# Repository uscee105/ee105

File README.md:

---
layout: home
title: USC EE 105
nav_exclude: true
permalink: /:path/
seo:
  type: Course
  name: EE 105
---

# Course website for USC EE 105

This introductory course offers a broad overview of electronic systems, integrating both hardware and software perspectives. Students will explore the fundamental building blocks of electronics, including basic circuits and key components such as resistors, capacitors, inductors, diodes, transistors, optoelectronic devices, and sensors. A central feature of the course is the hands-on design, construction, and testing of an optical biosensor that synthesizes concepts learned throughout the semester. Students will also be introduced to foundational topics in signals and systems, as well as neural networks, culminating in the implementation of a simple image classification system using embedded machine learning. Another major focus is on communication systems, particularly free-space optical communication, where students will build and experiment with paired light emitters and detectors. Hands-on learning is supported by a custom demonstration board, which includes modules for circuits, devices, system integration, and AI/ML-based image processing. In summary, this course provides an engaging introduction to electrical engineering, emphasizing experiential learning through the development of intelligent hardware and software systems.

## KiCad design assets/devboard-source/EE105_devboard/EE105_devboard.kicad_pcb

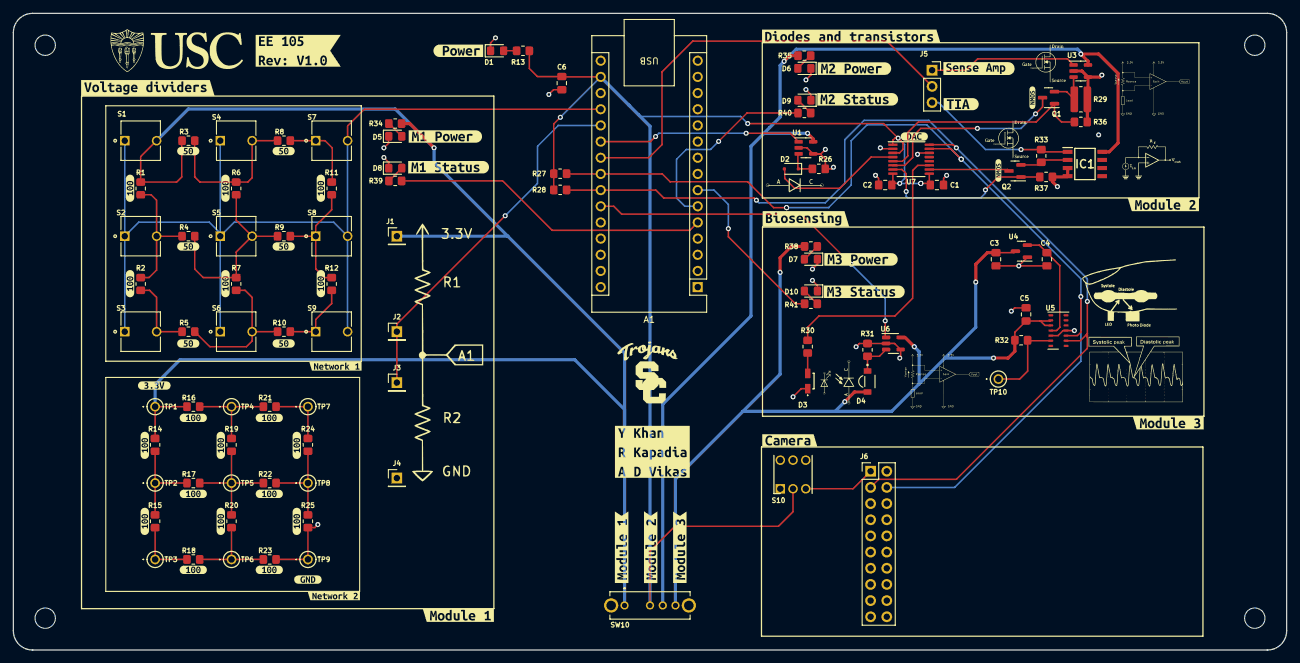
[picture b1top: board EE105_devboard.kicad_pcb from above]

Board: 2 copper layers, 200.0 x 100.0 mm, 150 parts (0 on the bottom side), 52 nets.

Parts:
A1: Arduino_Nano_Every; Arduino_Nano
C1, C5: 0.1uF; C_0805_2012Metric_Pad1.18x1.45mm_HandSolder
C2: 100nF; C_0805_2012Metric_Pad1.18x1.45mm_HandSolder
C3, C4, C6: 1uF; C_0805_2012Metric_Pad1.18x1.45mm_HandSolder
D1: PWR; LED_0805_2012Metric_Pad1.15x1.40mm_HandSolder
D2: D; D_SOD-323F
D3: PD_LED; CSL0416WBCW1
D4: VEMD2023SLX01; XDCR_VEMD2023SLX01
D5: m1_pwr; LED_0805_2012Metric_Pad1.15x1.40mm_HandSolder
D6: m2_pwr; LED_0805_2012Metric_Pad1.15x1.40mm_HandSolder
D7: m3_pwr; LED_0805_2012Metric_Pad1.15x1.40mm_HandSolder
D8: m1_status; LED_0805_2012Metric_Pad1.15x1.40mm_HandSolder
D9: m2_status; LED_0805_2012Metric_Pad1.15x1.40mm_HandSolder
D10: m3_status; LED_0805_2012Metric_Pad1.15x1.40mm_HandSolder
H1, H2, H3, H4: MountingHole; MountingHole_3.2mm_M3
IC1: TLV9102IDR; SOIC127P600X175-8N
J1, J2, J3, J4: Conn_01x01_Pin; PinHeader_1x01_P2.54mm_Vertical
J5: tia vs senseamp; PinSocket_1x03_P2.54mm_Vertical
J6: camera_connector; PinHeader_2x10_P2.54mm_Vertical
Q1, Q2: DMN3404L; SOT-23
R1, R2, R6, R7, R11, R12, R14, R15, R16, R17, R18, R19, R20, R21, R22, R23, R24, R25: 100; R_0805_2012Metric_Pad1.20x1.40mm_HandSolder
R3, R4, R5, R8, R9, R10: 50; R_0805_2012Metric_Pad1.20x1.40mm_HandSolder
R13, R30, R31, R34, R35, R36, R37, R38, R39, R40, R41: 1k; R_0805_2012Metric_Pad1.20x1.40mm_HandSolder
R26: 0.2; R_0805_2012Metric_Pad1.20x1.40mm_HandSolder
R27, R28: 4.7k; R_0805_2012Metric_Pad1.20x1.40mm_HandSolder
R29: 0.04; R_0815_2038Metric_Pad1.20x4.05mm_HandSolder
R32: 10k; R_0805_2012Metric_Pad1.20x1.40mm_HandSolder
R33: 1; R_0805_2012Metric_Pad1.20x1.40mm_HandSolder
S1, S2, S3, S4, S5, S6, S7, S8, S9: 4-1437565-0; SW_4-1437565-0
S10: MHPS2266; DIPS450W80P200L600H1050Q6N
SW10: pwr_select; OS103011MA7QP1
TP1, TP2, TP3, TP4, TP5, TP6, TP7, TP8, TP9, TP10: 5115
U1, U3, U6: INA180A1; SOT-23-5
U4: MCP1703T-1802E/CB; SOT-23
U5: MAX30102; Maxim_OLGA-14_3.3x5.6mm_P0.8mm
U7: AD5593R; TSSOP-16_4.4x5mm_P0.65mm
kibuzzard-666A1C01: G***; kibuzzard-666A1C01
kibuzzard-666A1C15: G***; kibuzzard-666A1C15
kibuzzard-666A1C72: G***; kibuzzard-666A1C72
kibuzzard-666A1D09: G***; kibuzzard-666A1D09
kibuzzard-666A1E2E: G***; kibuzzard-666A1E2E
kibuzzard-666A1E14: G***; kibuzzard-666A1E14
kibuzzard-666A1E29: G***; kibuzzard-666A1E29
kibuzzard-666A13FA: G***; kibuzzard-666A13FA
kibuzzard-666A15EB: G***; kibuzzard-666A15EB
kibuzzard-666A140F: G***; kibuzzard-666A140F
kibuzzard-666A176F: G***; kibuzzard-666A176F
kibuzzard-666A1613: G***; kibuzzard-666A1613
kibuzzard-666A1764: G***; kibuzzard-666A1764
kibuzzard-666B1BA9: G***; kibuzzard-666B1BA9
kibuzzard-666B1C5A, kibuzzard-666B1C5A#2, kibuzzard-666B1C5A#3, kibuzzard-666B1C5A#4, kibuzzard-666B1C5A#5, kibuzzard-666B1C5A#6, kibuzzard-666B1C5A#7, kibuzzard-666B1C5A#8, kibuzzard-666B1C5A#9, kibuzzard-666B1C5A#10, kibuzzard-666B1C5A#11, kibuzzard-666B1C5A#12, kibuzzard-666B1C5A#13, kibuzzard-666B1C5A#14, kibuzzard-666B1C5A#15, kibuzzard-666B1C5A#16, kibuzzard-666B1C5A#17, kibuzzard-666B1C5A#18: G***; kibuzzard-666B1C5A
kibuzzard-666B1CC3, kibuzzard-666B1CC3#2, kibuzzard-666B1CC3#3, kibuzzard-666B1CC3#4, kibuzzard-666B1CC3#5, kibuzzard-666B1CC3#6: G***; kibuzzard-666B1CC3
kibuzzard-666B6DEA, kibuzzard-666B6DEA#2: G***; kibuzzard-666B6DEA
kibuzzard-666B45CE: G***; kibuzzard-666B45CE
kibuzzard-666B70BB: G***; kibuzzard-666B70BB
kibuzzard-666B70CC: G***; kibuzzard-666B70CC
kibuzzard-666B462C: G***; kibuzzard-666B462C
kibuzzard-666B4306: G***; kibuzzard-666B4306
kibuzzard-666B4604: G***; kibuzzard-666B4604
kibuzzard-666B4618: G***; kibuzzard-666B4618
kibuzzard-666B7167: G***; kibuzzard-666B7167
kibuzzard-66690A5C: G***; kibuzzard-66690A5C
kibuzzard-66690A8E: G***; kibuzzard-66690A8E
kibuzzard-66690A76: G***; kibuzzard-66690A76
kibuzzard-66690AD5: G***; kibuzzard-66690AD5

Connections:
1v8_m3: C4.1, U4.2 (VO), U5.11 (VDD)
3v3: A1.17 (3V3), C1.1, C2.2, C6.1, R13.1, R27.1, R28.1, S10.2, SW10.2 (COM), U7.1 (~RESET), U7.3 (V_{DD}), U7.8 (V_{REF}), U7.9 (V_{LOGIC})
3v3_m1: J1.1, R1.1, R3.1, R14.1, R16.1, R34.1, S1.2, SW10.1 (NO), TP1.TP
3v3_m2: IC1.8 (V+), R35.1, SW10.3 (NC_1), U1.5 (V+), U3.5 (V+)
3v3_m3: C3.1, C5.2, D4.A, R32.1, R38.1, SW10.4 (NC_2), U4.3 (VI), U5.9 (VLED+), U5.10 (VLED+), U6.5 (V+)
/Module 1/center_node: R4.2, R6.2, R7.1, R9.1, S5.2
A0_NA: A1.19 (A0), S1.1, S2.1, S3.1, S4.1, S5.1, S6.1, S7.2, S8.2, S9.2
DAC_out0: D2.2 (A), U7.4 (IO0)
DAC_out1: Q1.1 (G), R36.1, U7.5 (IO1)
DAC_out2: Q1.3 (D), U7.6 (IO2)
DAC_out3: Q2.1 (G), R37.1, U7.7 (IO3)
DAC_out4: Q2.3 (D), U7.10 (IO4)
DAC_out5: R30.1, U7.11 (IO5)
unnamed: D1.2 (A), R13.2
unnamed: D2.1 (K), R26.1, U1.3 (+)
unnamed: D3.2 (A), R30.2
unnamed: D5.2 (A), R34.2
unnamed: D6.2 (A), R35.2
unnamed: D7.2 (A), R38.2
unnamed: D8.2 (A), R39.2
unnamed: D9.2 (A), R40.2
unnamed: D10.2 (A), R41.2
unnamed: J6.1, S10.3
unnamed: Q1.2 (S), R29.1, U3.3 (+)
unnamed: R1.2, R2.1, R4.1, S2.2
unnamed: R2.2, R5.1, S3.2
unnamed: R3.2, R6.1, R8.1, S4.2
unnamed: R5.2, R7.2, R10.1, S6.2
unnamed: R8.2, R11.1, S7.1
unnamed: R9.2, R11.2, R12.1, S8.1
unnamed: R14.2, R15.1, R17.1, TP2.TP
unnamed: R15.2, R18.1, TP3.TP
unnamed: R16.2, R19.1, R21.1, TP4.TP
unnamed: R17.2, R19.2, R20.1, R22.1, TP5.TP
unnamed: R18.2, R20.2, R23.1, TP6.TP
unnamed: R21.2, R24.1, TP7.TP
unnamed: R22.2, R24.2, R25.1, TP8.TP
unnamed: R32.2, TP10.TP, U5.13 (~INT)
unnamed: D4.C, R31.1, U6.3 (+)
SCL: A1.24 (SCL/A5), J6.3, R28.2, U5.2 (SCL), U7.16 (SCL)
SDA: A1.23 (SDA/A4), J6.4, R27.2, U5.3 (SDA), U7.15 (SDA)
gnd: A1.4 (GND), A1.29 (GND), C1.2, C2.1, C3.2, C4.2, C5.1, C6.2, D1.1 (K), D3.1 (K), D5.1 (K), D6.1 (K), D7.1 (K), D8.1 (K), D9.1 (K), D10.1 (K), IC1.3 (IN1+), IC1.4 (V-), J4.1, J6.2, R10.2, R12.2, R23.2, R25.2, R26.2, R29.2, R31.2, R36.2, R37.2, S9.1, TP9.TP, U1.2 (GND), U1.4 (-), U3.2 (GND), U3.4 (-), U4.1 (GND), U5.4 (PGND), U5.12 (GND), U6.2 (GND), U6.4 (-), U7.2 (A0), U7.14 (GND)
m1_status_led: A1.5 (D2), R39.1
m1_voltage_divider: A1.20 (A1), J2.1, J3.1
m2_diode: A1.21 (A2), U1.1
m2_nmos: A1.22 (A3), J5.2
m2_nmos_senseamp: J5.1, U3.1
m2_nmos_tia: IC1.1 (OUT1), J5.3, R33.1
m2_status_led: A1.6 (D3), R40.1
m3_photo_diode: A1.25 (A6), U6.1
m3_status_led: A1.7 (D4), R41.1
source: IC1.2 (IN1-), Q2.2 (S), R33.2

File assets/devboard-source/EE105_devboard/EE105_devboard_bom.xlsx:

Ref | Qnty | Value | Cmp name | Footprint | Mouser | Amazon link
A1 | 1 | Arduino_Nano_Every | Arduino_Nano_Every | Module:Arduino_Nano | DNP | DNP
C1, C5 | 2 | 0.1uF | C | Capacitor_SMD:C_0805_2012Metric_Pad1.18x1.45mm_HandSolder | https://www.mouser.com/ProductDetail/Murata-Electronics/GCD2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
C2 | 1 | 100nF | C | Capacitor_SMD:C_0805_2012Metric_Pad1.18x1.45mm_HandSolder | https://www.mouser.com/ProductDetail/Murata-Electronics/GCD2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
C3, C4, C6 | 3 | 1uF | C | Capacitor_SMD:C_0805_2012Metric_Pad1.18x1.45mm_HandSolder | https://www.mouser.com/ProductDetail/Murata-Electronics/GRM2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
D1 | 1 | PWR | LED | LED_SMD:LED_0805_2012Metric_Pad1.15x1.40mm_HandSolder | https://www.mouser.com/ProductDetail/Wurth-Elektronik/150080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
D2 | 1 | D | D | Diode_SMD:D_0805_2012Metric_Pad1.15x1.40mm_HandSolder | https://www.mouser.com/ProductDetail/Nexperia/BAS321115?qs=m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
D3 | 1 | PD_LED | LED | custom_footprints:CSL0416WBCW1 | https://www.mouser.com/ProductDetail/ROHM-Semiconductor/CSL0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
D4 | 1 | VEMD2023SLX01 (Photo Diode) | VEMD2023SLX01 | custom_footprints:XDCR_VEMD2023SLX01 | https://www.mouser.com/ProductDetail/Vishay-Semiconductors/V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
D5 | 1 | m1_pwr | LED | LED_SMD:LED_0805_2012Metric_Pad1.15x1.40mm_HandSolder | https://www.mouser.com/ProductDetail/Wurth-Elektronik/150080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
D6 | 1 | m2_pwr | LED | LED_SMD:LED_0805_2012Metric_Pad1.15x1.40mm_HandSolder | https://www.mouser.com/ProductDetail/Wurth-Elektronik/150080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
D7 | 1 | m3_pwr | LED | LED_SMD:LED_0805_2012Metric_Pad1.15x1.40mm_HandSolder | https://www.mouser.com/ProductDetail/Wurth-Elektronik/150080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
D8 | 1 | m1_status | LED | LED_SMD:LED_0805_2012Metric_Pad1.15x1.40mm_HandSolder | https://www.mouser.com/ProductDetail/Wurth-Elektronik/150080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
D9 | 1 | m2_status | LED | LED_SMD:LED_0805_2012Metric_Pad1.15x1.40mm_HandSolder | https://www.mouser.com/ProductDetail/Wurth-Elektronik/150080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
D10 | 1 | m3_status | LED | LED_SMD:LED_0805_2012Metric_Pad1.15x1.40mm_HandSolder | https://www.mouser.com/ProductDetail/Wurth-Elektronik/150080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
H1, H2, H3, H4 | 4 | MountingHole | MountingHole | MountingHole:MountingHole_3.2mm_M3 | DNP | DNP
IC1 | 1 | TLV9102IDR | TLV9102IDR | custom_footprints:SOIC127P600X175-8N | https://www.mouser.com/ProductDetail/Texas-Instruments/TLV91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
J1, J2, J3, J4 | 4 | Conn_01x01_Pin | Conn_01x01_Pin | Connector_PinHeader_2.54mm:PinHeader_1x01_P2.54mm_Vertical | DNP | DNP
J5 | 1 | tia vs senseamp | Conn_01x03_Pin | Connector_PinSocket_2.54mm:PinSocket_1x03_P2.54mm_Vertical | DNP | DNP
J6 | 1 | camera_connector | Conn_02x10_Odd_Even | Connector_PinHeader_2.54mm:PinHeader_2x10_P2.54mm_Vertical | DNP | DNP
Q1, Q2 | 2 | DMN3404L | DMN3404L | Package_TO_SOT_SMD:SOT-23 | https://www.mouser.com/ProductDetail/Diodes-Incorporated/DMN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
R1, R2, R6, R7, R11, R12, R14, R15, R16, R17, R18, R19, R20, R21, R22, R23, R24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 | 18 | 100 | R | Resistor_SMD:R_0805_2012Metric_Pad1.20x1.40mm_HandSolder | https://www.mouser.com/ProductDetail/Vishay-Dale/CRCW0805100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
R3, R4, R5, R8, R9, R10 | 6 | 50 | R | Resistor_SMD:R_0805_2012Metric_Pad1.20x1.40mm_HandSolder | https://www.mouser.com/ProductDetail/Vishay-Dale/CRCW080551R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
R13, R30, R31, R34, R35, R36, R37, R38, R39, R40, R41 | 11 | 1k | R | Resistor_SMD:R_0805_2012Metric_Pad1.20x1.40mm_HandSolder | https://www.mouser.com/ProductDetail/Vishay-Dale/CRCW08051K0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
R26 | 1 | 0.2 | R | Resistor_SMD:R_0805_2012Metric_Pad1.20x1.40mm_HandSolder | https://www.mouser.com/ProductDetail/Panasonic/ERJ-6DSFR20V?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
R27, R28 | 2 | 4.7k | R | Resistor_SMD:R_0805_2012Metric_Pad1.20x1.40mm_HandSolder | https://www.mouser.com/ProductDetail/Vishay-Dale/CRCW08054K7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
R29 | 1 | 0.04 | R | Resistor_SMD:R_0805_2012Metric_Pad1.20x1.40mm_HandSolder | https://www.mouser.com/ProductDetail/ROHM-Semiconductor/LTR1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
R32 | 1 | 10k | R | Resistor_SMD:R_0805_2012Metric_Pad1.20x1.40mm_HandSolder | https://www.mouser.com/ProductDetail/Vishay-Dale/RCS080510K0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
R33 | 1 | 1 | R | Resistor_SMD:R_0805_2012Metric_Pad1.20x1.40mm_HandSolder | https://www.mouser.com/ProductDetail/Vishay-Dale/RCS08051R00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
S1, S2, S3, S4, S5, S6, S7, S8, S9 | 9 | 4-1437565-0 | 4-1437565-0 | custom_footprints:SW_4-1437565-0 | https://www.mouser.com/ProductDetail/TE-Connectivity-Alcoswi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
S10 | 1 | MHPS2266 | MHPS2266 | custom_footprints:DIPS450W80P200L600H1050Q6N | https://www.mouser.com/ProductDetail/Apem/MHPS2266?qs=%2Fs1L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
SW10 | 1 | pwr_select | OS103011MA7QP1 | custom_footprints:OS103011MA7QP1 | https://www.mouser.com/ProductDetail/CK/OS103011MA7QP1?qs=Wt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
TP1, TP2, TP3, TP4, TP5, TP6, TP7, TP8, TP9, TP10 | 10 | 5115 | 5115 | custom_footprints:5115 | https://www.mouser.com/ProductDetail/Keystone-Electronics/51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
U1, U3, U6 | 3 | INA180A1 | INA180A1 | Package_TO_SOT_SMD:SOT-23-5 | https://www.mouser.com/ProductDetail/Texas-Instruments/INA18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
U4 | 1 | MCP1703T-1802E/CB | MCP1703Ax-180xxTT | Package_TO_SOT_SMD:SOT-23 | https://www.mouser.com/ProductDetail/Microchip-Technology/MC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
U5 | 1 | MAX30102 | MAX30102 | OptoDevice:Maxim_OLGA-14_3.3x5.6mm_P0.8mm | https://www.mouser.com/ProductDetail/Analog-Devices-Maxim-In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
U7 | 1 | AD5593R | AD5593R | Package_SO:TSSOP-16_4.4x5mm_P0.65mm | https://www.mouser.com/ProductDetail/Analog-Devices/AD5593RB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

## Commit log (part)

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2025-08-02 updating files
2025-08-02 schedule done
2025-08-02 domain change
2025-08-02 Revert "domain change"
    This reverts commit a21cb647b34da71decb6f8324c9ca1966984b471.
2025-08-02 Create CNAME
2025-08-02 domain check
2025-08-02 domain fixed
2025-08-02 mod updates
2025-08-02 merging files from fall 24
2025-08-02 merges sp 25
2025-08-03 mod 1 fixes
2025-08-03 fix upto mod 2
2025-08-03 mod 3 update
2025-08-03 mod 4 update
2025-08-03 mod 5 update
2025-08-03 v1 is ready
2025-08-19 updated calendar for week 1
2025-08-26 lec 1 update
2025-08-30 python bootcamp update
2025-08-31 bootcamp change
2025-09-01 hw1 released
2025-09-07 circuit update
2025-09-07 circuit update 2
2025-09-08 office hours
2025-09-11 hw 2 released
2025-09-16 circuit 3 update
2025-09-17 circuit 4 update
2025-09-23 device update
2025-09-23 device update 2
2025-09-23 hw 3 released
2025-09-24 update lec 2 of dev
2025-09-28 device final
2025-09-30 practice mid
2025-10-11 sensor update
2025-10-15 sensors file update
2025-10-20 lab file update
2025-10-21 hw 4 upload
2025-10-28 ml and team update
2025-10-30 nn update
2025-11-02 hw 5
2025-11-03 lifi
2025-11-12 comm update
2025-11-18 sensor fusion
2025-11-20 practice final up
2025-11-21 hw6 update
2025-12-02 reading list
2025-12-02 pdf update
2025-12-17 remove pdfs
2026-01-11 spring 26 start
2026-01-11 sp setup
2026-01-13 added TA
2026-01-20 arduino
2026-01-27 calendar update
2026-01-28 gradescope update
2026-02-03 lab update
2026-02-10 hw 2 up
2026-02-10 updarte hw2
2026-02-10 hw 3 up
2026-02-17 lec 10 update
2026-02-24 mid sol
2026-03-10 oximeter lab update
2026-03-24 final groups
2026-03-25 final team
2026-03-26 ml lab update
2026-03-26 nn lab update
2026-04-07 arduino nn
2026-04-07 lab checkoff
2026-04-12 hw upload
2026-04-12 lab tour
2026-04-14 comm lab update
2026-04-27 practice final solution
2026-04-30 poll
